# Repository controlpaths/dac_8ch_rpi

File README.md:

# 8-ch Analog output board

The DAC-8CH-RPI board features 8 analog outputs, 8 digital inputs and 4 digital outputs. It is intended to be used in real-time hardware simulators or signal generators. 

## Analog outputs

The board features an 8-channel DAC with a resolution of 12 bits, and a sampling rate of up to 100ksps. 

The output range goes from -3V to 3V.

## Raspberry Pi connector

The board features a 40-pin Raspberry PI Connector with the SPI interface for the DAc and the digital in-out.

This connector is compatible with FPGA boards such as Pynq-Z1, Pynq-Z2,AMD KR260 or MPFS Discovery Kit.

## Get Yours

The RP2040 PMOD is open-source, so you can use the output files to manufacture your own in [JLCPCB](https://jlcpcb.com/?from=controlpath). You just need to compress the `production_files` directory, and upload it to [JLCPCB](https://jlcpcb.com/?from=controlpath). 

Remember to change the Surface Finish to **LeadFree HASL** to make your board ROHS compliant.

Then you have to add the PCB Assembly service and upload the [centroid](./kicad/production_files/ohsim_hat_pos.csv) file, and the [BOM](./kicad/production_files/bom.csv). 

In a few days, you will receive your board at home.

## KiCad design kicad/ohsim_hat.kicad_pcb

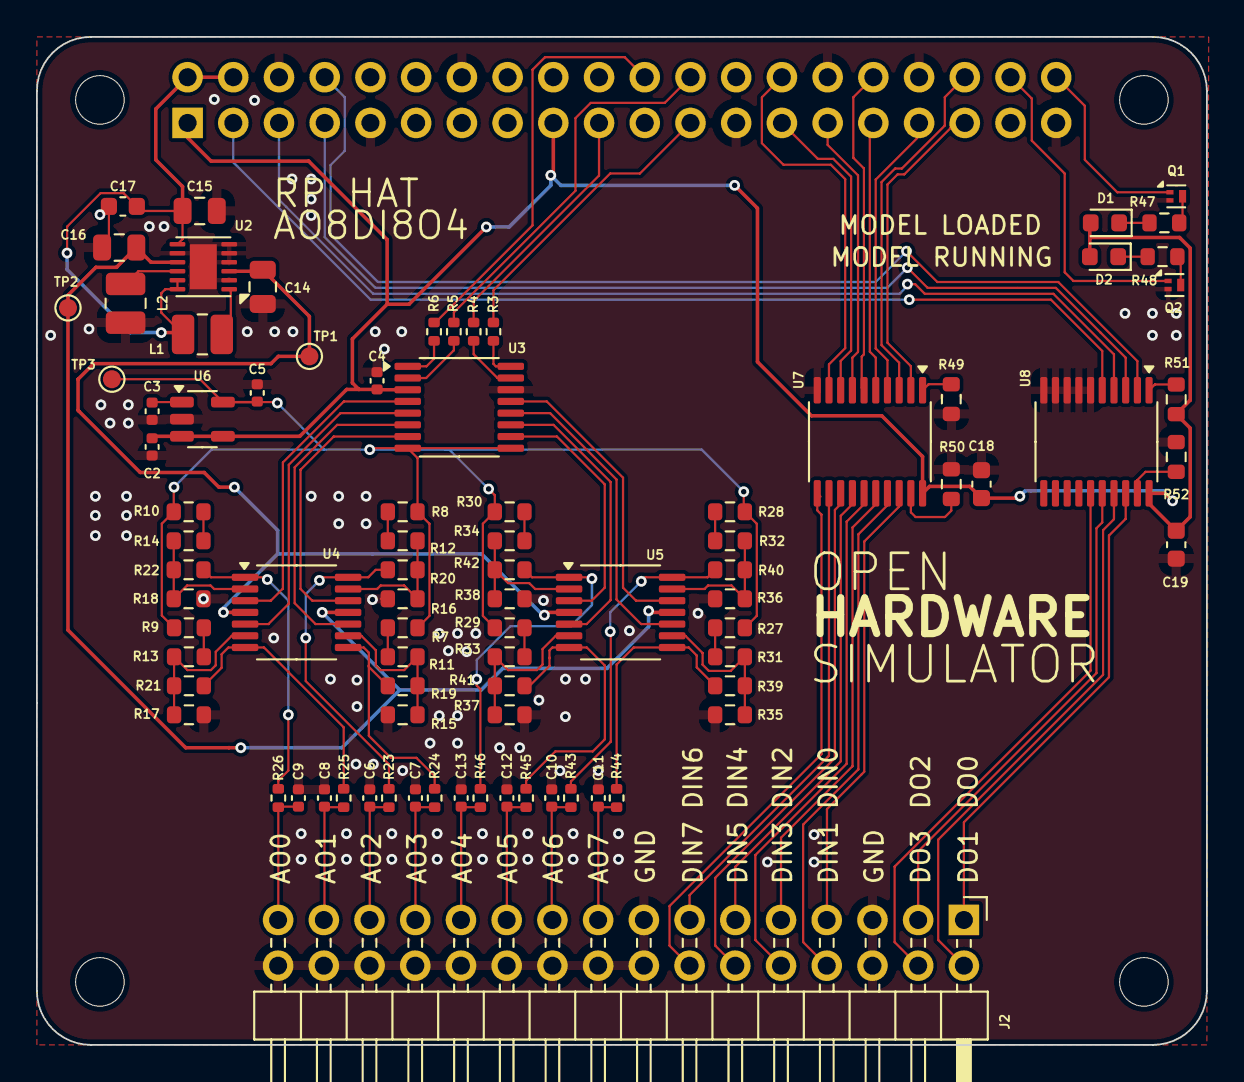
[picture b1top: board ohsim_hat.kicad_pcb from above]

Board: 2 copper layers, 65.0 x 56.0 mm, 90 parts (1 on the bottom side), 91 nets.

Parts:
C2, C4: 0.47u; C_0402_1005Metric
C3, C5: 100n; C_0402_1005Metric
C6, C7, C8, C9, C10, C11, C12, C13: 1n5; C_0402_1005Metric
C14, C15, C16: 10u; C_0805_2012Metric
C17, C18, C19: 100n; C_0603_1608Metric
D1, D2: LED; LED_0603_1608Metric
J1: GPIO; PinSocket_2x20_P2.54mm_Vertical
J2: Conn_02x16_Odd_Even; PinHeader_2x16_P2.54mm_Horizontal
L1, L2: 4u7; L_1008_2520Metric
MH1, MH2, MH3, MH4: MountingHole_2.7mm_M2.5
Q1, Q2: DMN26D0UFB4-7; Diodes_DFN1006-3
R3, R4, R5, R6: 27; R_0402_1005Metric
R7, R8, R9, R10, R27, R28, R29, R30: 8k; R_0603_1608Metric
R11, R12, R13, R14, R31, R32, R33, R34, R47, R48: 330; R_0603_1608Metric
R15, R16, R17, R18, R35, R36, R37, R38: 50k; R_0603_1608Metric
R19, R20, R21, R22, R39, R40, R41, R42, R49, R50, R51, R52: 10k; R_0603_1608Metric
R23, R24, R25, R26, R43, R44, R45, R46: 1k; R_0402_1005Metric
TP1, TP2, TP3: TestPoint; TestPoint_Pad_D1.0mm
U2: WSON-12-1EP_3x3mm_P0.5mm_EP1.5x2.5mm
U3: AD53x8; TSSOP-16_4.4x5mm_P0.65mm
U4, U5: OPA4990; TSSOP-14_4.4x5mm_P0.65mm
U6: REF2025; SOT-23-5
U7, U8: 74HC245; TSSOP-20_4.4x6.5mm_P0.65mm

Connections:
+3V3: C2.2, C4.1, C18.2, C19.2, D1.2 (A), D2.2 (A), J1.1, J1.17, R51.1, U3.3 (VDD), U6.3 (EN), U6.4 (IN), U7.20 (VCC), U8.20 (VCC)
+5V: C14.1, TP1.1, U2.3 (VPOS), U4.4 (V+), U5.4 (V+)
-5V: C16.1, TP2.1, U2.9 (VNEG), U4.11 (V-), U5.11 (V-)
AOUT0: C9.1, J2.31, R26.2
AOUT1: C8.1, J2.29, R25.2
AOUT2: C6.1, J2.27, R23.2
AOUT3: C7.1, J2.25, R24.2
AOUT4: C13.1, J2.23, R46.2
AOUT5: C12.1, J2.21, R45.2
AOUT6: C10.1, J2.19, R43.2
AOUT7: C11.1, J2.17, R44.2
DAC_CH0: U3.4 (VOUT_A), U4.3 (+)
DAC_CH1: U3.5 (VOUT_B), U4.5 (+)
DAC_CH2: U3.6 (VOUT_C), U4.10 (+)
DAC_CH3: U3.7 (VOUT_D), U4.12 (+)
DAC_CH4: U3.10 (VOUT_E), U5.3 (+)
DAC_CH5: U3.11 (VOUT_F), U5.5 (+)
DAC_CH6: U3.12 (VOUT_G), U5.10 (+)
DAC_CH7: U3.13 (VOUT_H), U5.12 (+)
DAC_DIN: J1.19, R4.2
DAC_LDAC: J1.22, R6.2
DAC_REF: C5.1, R7.1, R8.1, R9.1, R10.1, R27.1, R28.1, R29.1, R30.1, TP3.1, U3.8 (VREF_ABCD), U3.9 (VREF_EFGH), U6.5 (Vref)
DAC_SCLK: J1.23, R3.2
DAC_SYNC: J1.24, R5.2
DI0: J1.35, U7.2 (A0)
DI0_CONN: J2.7, U7.18 (B0)
DI1: J1.36, U7.3 (A1)
DI1_CONN: J2.8, U7.17 (B1)
DI2: J1.33, U7.4 (A2)
DI2_CONN: J2.9, U7.16 (B2)
DI3: J1.31, U7.5 (A3)
DI3_CONN: J2.10, U7.15 (B3)
DI4: J1.32, U7.6 (A4)
DI4_CONN: J2.11, U7.14 (B4)
DI5: J1.29, U7.7 (A5)
DI5_CONN: J2.12, U7.13 (B5)
DI6: J1.27, U7.8 (A6)
DI6_CONN: J2.13, U7.12 (B6)
DI7: J1.28, U7.9 (A7)
DI7_CONN: J2.14, U7.11 (B7)
DO0: J1.8, U8.2 (A0)
DO0_CONN: J2.1, U8.18 (B0)
DO1: J1.7, U8.3 (A1)
DO1_CONN: J2.2, U8.17 (B1)
DO2: J1.5, U8.4 (A2)
DO2_CONN: J2.3, U8.16 (B2)
DO3: J1.3, U8.5 (A3)
DO3_CONN: J2.4, U8.15 (B3)
GND: C2.1, C3.2, C4.2, C5.2, C6.2, C7.2, C8.2, C9.2, C10.2, C11.2, C12.2, C13.2, C14.2, C15.2, C16.2, C17.2, C18.1, C19.1, J1.6, J1.9, J1.14, J1.20, J1.25, J1.30, J1.34, J1.39, J2.5, J2.6, J2.15, J2.16, J2.18, J2.20, J2.22, J2.24, J2.26, J2.28, J2.30, J2.32, L2.2, Q1.2, Q2.2, R15.1, R16.1, R17.1, R18.1, R35.1, R36.1, R37.1, R38.1, R49.1, R50.1, R52.1, U2.2 (PGND), U2.4 (GND), U2.5 (AGND), U2.6 (GND), U2.8 (GND), U2.13 (EP), U3.14 (GND), U6.2 (GND), U7.10 (GND), U8.6 (A4), U8.7 (A5), U8.8 (A6), U8.9 (A7), U8.10 (GND)
LED0: J1.40, Q1.1
LED1: J1.38, Q2.1
unnamed: D1.1 (K), R47.1
unnamed: D2.1 (K), R48.1
unnamed: Q1.3, R47.2
unnamed: Q2.3, R48.2
unnamed: R10.2, R14.1
unnamed: R7.2, R11.1
unnamed: R8.2, R12.1
unnamed: R9.2, R13.1
unnamed: R19.2, R24.1, U4.8
unnamed: R20.2, R23.1, U4.14
unnamed: R21.2, R25.1, U4.7
unnamed: R22.2, R26.1, U4.1
unnamed: R27.2, R31.1
unnamed: R28.2, R32.1
unnamed: R29.2, R33.1
unnamed: R30.2, R34.1
unnamed: R39.2, R44.1, U5.8
unnamed: R40.2, R43.1, U5.14
unnamed: R41.2, R45.1, U5.7
unnamed: R42.2, R46.1, U5.1
unnamed: L2.1, U2.10 (SWN)
unnamed: L1.2, U2.1 (SWP)
unnamed: R4.1, U3.15 (DIN)
unnamed: R3.1, U3.16 (SCLK)
unnamed: R6.1, U3.1 (~LDAC)
unnamed: R5.1, U3.2 (~SYNC)
unnamed: R14.2, R18.2, R22.1, U4.2 (-)
unnamed: R13.2, R17.2, R21.1, U4.6 (-)
unnamed: R11.2, R15.2, R19.1, U4.9 (-)
unnamed: R12.2, R16.2, R20.1, U4.13 (-)
unnamed: R34.2, R38.2, R42.1, U5.2 (-)
unnamed: R33.2, R37.2, R41.1, U5.6 (-)
unnamed: R31.2, R35.2, R39.1, U5.9 (-)
unnamed: R32.2, R36.2, R40.1, U5.13 (-)
unnamed: C3.1, U6.1 (Vbias)
unnamed: R49.2, U7.1 (A->B)
unnamed: R50.2, U7.19 (CE)
unnamed: R51.2, U8.1 (A->B)
unnamed: R52.2, U8.19 (CE)
VCC: C15.1, C17.1, J1.2, J1.4, L1.1, U2.7 (EN), U2.11 (AVIN), U2.12 (PVIN)

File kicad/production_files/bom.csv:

Reference,Value,Footprint,Qty,JLCPCB Part #
"C2,C4",0.47u,Capacitor_SMD:C_0402_1005Metric,2,C106255
"C3,C5",100n,Capacitor_SMD:C_0402_1005Metric,2,C1525
"C6,C7,C8,C9,C10,C11,C12,C13",1n5,Capacitor_SMD:C_0402_1005Metric,8,C23967
"C14,C15,C16",10u,Capacitor_SMD:C_0805_2012Metric,3,C86038
"C17,C18,C19",100n,Capacitor_SMD:C_0603_1608Metric,3,C1590
"D1,D2",LED,LED_SMD:LED_0603_1608Metric,2,C2288
J1,GPIO,Connector_PinSocket_2.54mm:PinSocket_2x20_P2.54mm_Vertical,1,C50982
J2,Conn_02x16_Odd_Even,Connector_PinHeader_2.54mm:PinHeader_2x16_P2.54mm_Horizontal,1,C97095
"L1,L2",4u7,Inductor_SMD:L_1008_2520Metric,2,C882976
"Q1,Q2",DMN26D0UFB4-7,Package_DFN_QFN:Diodes_DFN1006-3,2,C7525126
"R3,R4,R5,R6",27,Resistor_SMD:R_0402_1005Metric,4,C25100
"R7,R8,R9,R10,R27,R28,R29,R30",8k,Resistor_SMD:R_0603_1608Metric,8,C862311
"R11,R12,R13,R14,R31,R32,R33,R34,R47,R48",330,Resistor_SMD:R_0603_1608Metric,10,C22104
"R15,R16,R17,R18,R35,R36,R37,R38",50k,Resistor_SMD:R_0603_1608Metric,8,C304067
"R19,R20,R21,R22,R39,R40,R41,R42,R49,R50,R51,R52",10k,Resistor_SMD:R_0603_1608Metric,12,C15401
"R23,R24,R25,R26,R43,R44,R45,R46",1k,Resistor_SMD:R_0402_1005Metric,8,C409681
U2,~,Package_SON:WSON-12-1EP_3x3mm_P0.5mm_EP1.5x2.5mm,1,C134100
U3,AD53x8,Package_SO:TSSOP-16_4.4x5mm_P0.65mm,1,C578186
"U4,U5",OPA4990,Package_SO:TSSOP-14_4.4x5mm_P0.65mm,2,C2862600
U6,REF2025,Package_TO_SOT_SMD:SOT-23-5,1,C962078
"U7,U8",74HC245,Package_SO:TSSOP-20_4.4x6.5mm_P0.65mm,2,C37101

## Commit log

2025-03-30 fixed path
2025-03-30 fixed bom path
